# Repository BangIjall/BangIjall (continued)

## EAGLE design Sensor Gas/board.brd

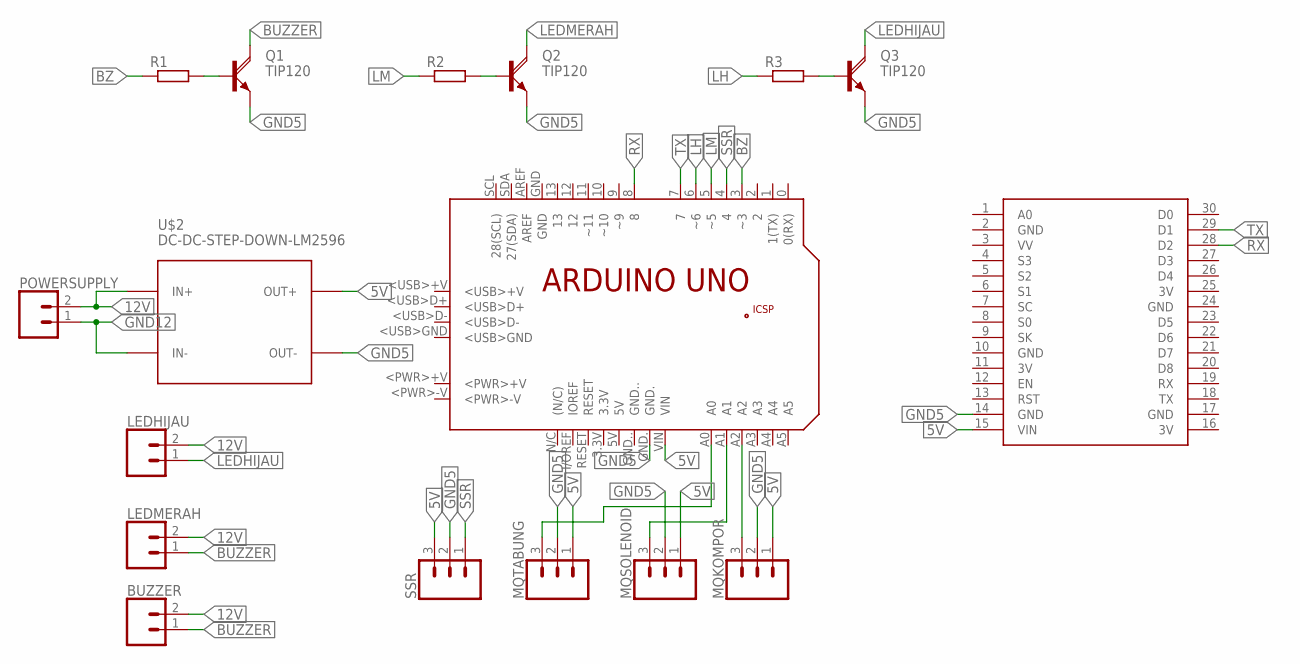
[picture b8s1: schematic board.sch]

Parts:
BUZZER: CONN_02; 1X02
LEDHIJAU: CONN_02; 1X02
LEDMERAH: CONN_02; 1X02
MQKOMPOR: CONN_03; 1X03
MQSOLENOID: CONN_03; 1X03
MQTABUNG: CONN_03; 1X03
PCB2: ARDUINO_UNO
POWERSUPPLY: CONN_02; 1X02
Q1, Q2, Q3: TIP120; TO220AH
R1, R2, R3: R-EU_0207/10; 0207/10
SSR: CONN_03; 1X03
U$1: NODEMCU
U$2: DC-DC-STEP-DOWN-LM2596

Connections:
3V: U$1.11 (3V), U$1.16 (3V), U$1.25 (3V)
5V: MQKOMPOR.1, MQSOLENOID.1, MQTABUNG.1, PCB2.VIN, SSR.3, U$1.15 (VIN), U$2.OUT+
12V: BUZZER.2, LEDHIJAU.2, LEDMERAH.2, POWERSUPPLY.2, U$2.IN+
BUZZER: BUZZER.1, LEDMERAH.1, Q1.C
BZ: PCB2.3 (~3), R1.1
GND: U$1.2 (GND), U$1.10 (GND), U$1.17 (GND), U$1.24 (GND)
GND5: MQKOMPOR.2, MQSOLENOID.2, MQTABUNG.2, PCB2.GND., Q1.E, Q2.E, Q3.E, SSR.2, U$1.14 (GND), U$2.OUT-
GND12: POWERSUPPLY.1, U$2.IN-
LEDHIJAU: LEDHIJAU.1, Q3.C
LEDMERAH: Q2.C
LH: PCB2.6 (~6), R3.1
LM: PCB2.5 (~5), R2.1
unnamed: Q1.B, R1.2
unnamed: MQSOLENOID.3, PCB2.A1
unnamed: MQTABUNG.3, PCB2.A0
unnamed: MQKOMPOR.3, PCB2.A2
unnamed: Q2.B, R2.2
unnamed: Q3.B, R3.2
RX: PCB2.8, U$1.28 (D2)
SSR: PCB2.4, SSR.1
TX: PCB2.7, U$1.29 (D1)

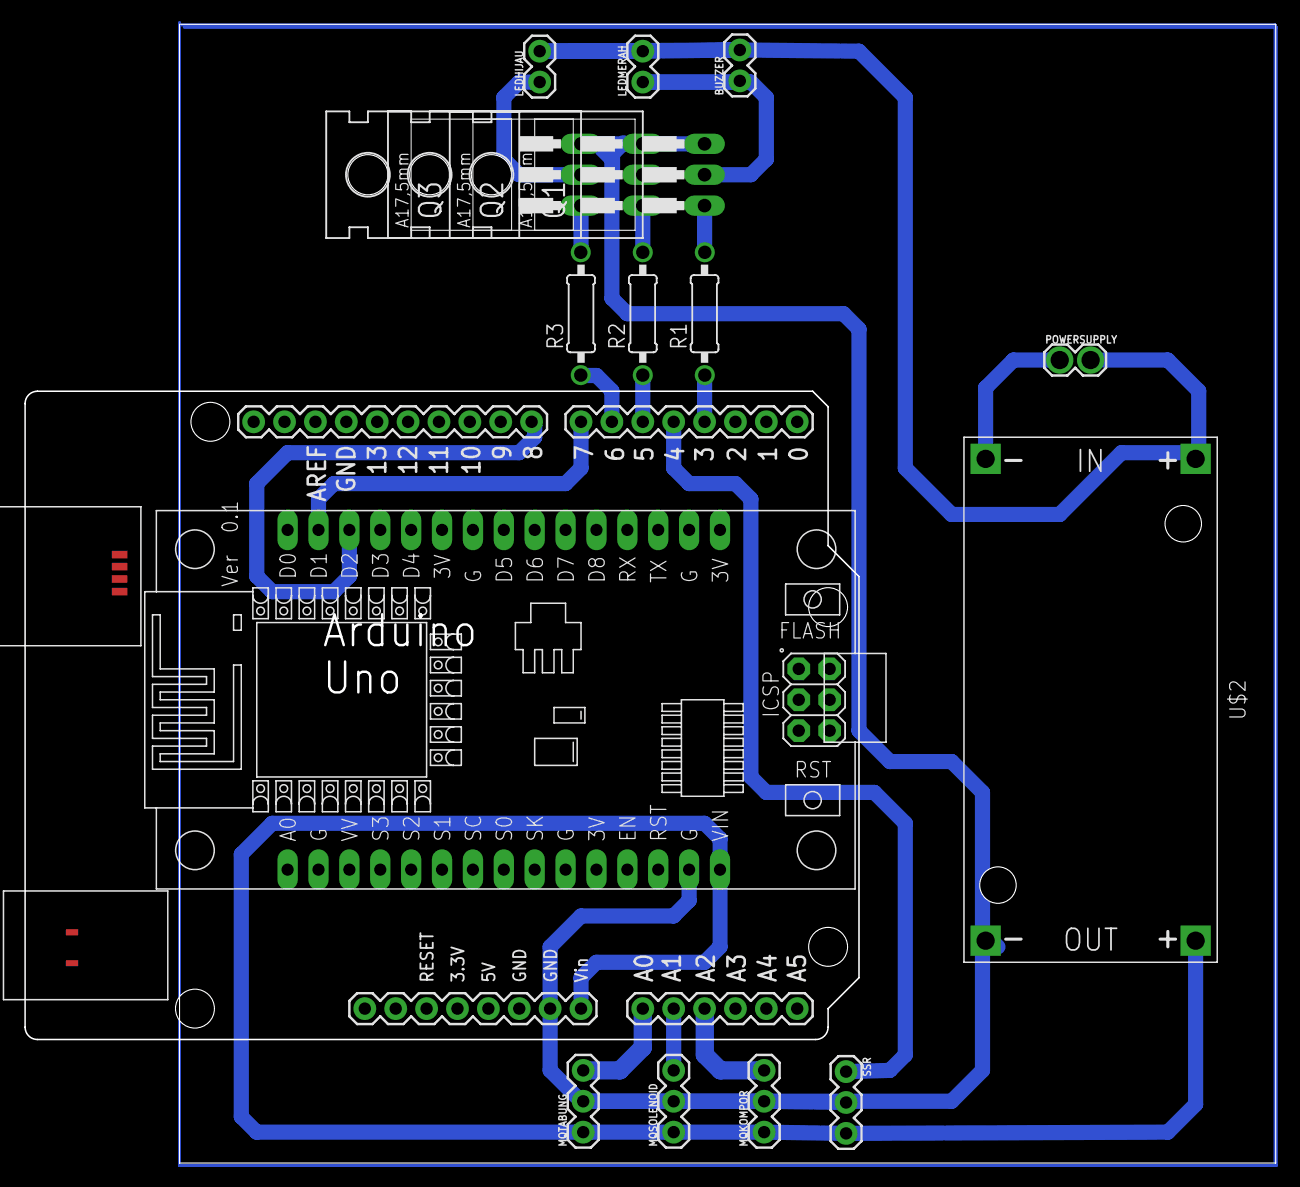
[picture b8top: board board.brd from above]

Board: 2 copper layers, 102.9 x 93.7 mm, 17 parts (0 on the bottom side), 20 nets.

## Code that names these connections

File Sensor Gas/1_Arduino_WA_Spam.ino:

#include <Arduino.h>
#include <SoftwareSerial.h>
#define rx_pin 8
#define tx_pin 7
SoftwareSerial data(rx_pin, tx_pin);
const float RL = 1;
const float clean_air_ratio = 10.0;
float adc, RS, Ro, RsRo, ppm, v;
float adc1, RS1, Ro1, RsRo1, ppm1, v1;
float adc2, RS2, Ro2, RsRo2, ppm2, v2;
const int SSR = 4;
const int buzzer = 3;
const int ledmerah = 5;
const int ledhijau = 6;
void kirimdata();
void setup()
{
  Serial.begin(9600);
  data.begin(115200);
  pinMode(buzzer, OUTPUT);
  pinMode(SSR, OUTPUT);
  pinMode(ledmerah, OUTPUT);
  pinMode(ledhijau, OUTPUT);
  pinMode(A0, INPUT);
  pinMode(A1, INPUT);
  pinMode(A2, INPUT);
  //sensor MQ di tabung
  int adc = analogRead(A0);
  v = adc * 5 / 1023.00;
  RS = ((5 * RL / v) - RL);
  Ro = RS / clean_air_ratio;
  delay(1000);

  //sensor MQ di SSR solenoid valve
  int adc1 = analogRead(A1);
  v1 = adc1 * 5 / 1023.00;
  RS1 = ((5 * RL / v1) - RL);
  Ro1 = RS1 / clean_air_ratio;
  delay(1000);

  //sensor MQ kompor
  int adc2 = analogRead(A2);
  v2 = adc2 * 5 / 1023.00;
  RS2 = ((5 * RL / v2) - RL);
  Ro2 = RS2 / clean_air_ratio;
  delay(1000);
}

void loop()
{
  kirimdata();
}

void kirimdata()
{
  //sensor MQ di tabung gas
  do
  {
  int adc = analogRead(A0);
  v = adc * 5 / 1023.00;
  RS = ((5 * RL / v) - RL);
  RsRo = RS / Ro;
  ppm = 1099.6 * pow((RsRo), -2.31);
  if (ppm >= 1000)
  {
    digitalWrite(buzzer, HIGH); // switch buzzer off
    digitalWrite(SSR, HIGH);
    digitalWrite(ledmerah, HIGH);
    digitalWrite(ledhijau, LOW);
    String datakirim = "a";
    Serial.println(datakirim);
    data.print(datakirim);
    data.write(13);
    delay(1000);
  }
  else
  {
    digitalWrite(buzzer, LOW); // switch buzzer on for 100ms
    digitalWrite(SSR, LOW);
    digitalWrite(ledmerah, LOW);
    digitalWrite(ledhijau, HIGH);
  }
  }
  while(ppm>=1000);

  //sensor MQ di SSR solenoid valve
  do
  {
  int adc1 = analogRead(A1);
  v1 = adc1 * 5 / 1023.00;
  RS1 = ((5 * RL / v1) - RL);
  RsRo1 = RS1 / Ro1;
  ppm1 = 1099.6 * pow((RsRo1), -2.31);

  if (ppm1 >= 1000)
  {
    digitalWrite(buzzer, HIGH); // switch buzzer off
    digitalWrite(SSR, HIGH);
    digitalWrite(ledmerah, HIGH);
    digitalWrite(ledhijau, LOW);
    String datakirim1 = "b";
    Serial.println(datakirim1);
    data.print(datakirim1);
    data.write(13);
    delay(1000);
  }
  else
  {
    digitalWrite(buzzer, LOW); // switch buzzer on for 100ms
    digitalWrite(SSR, LOW);
    digitalWrite(ledmerah, LOW);
    digitalWrite(ledhijau, HIGH);
  }
  }
   while(ppm1>=1000);

  //sensor MQ di kompor
  do
  {
  int adc2 = analogRead(A2);
  v2 = adc2 * 5 / 1023.00;
  RS2 = ((5 * RL / v2) - RL);
  RsRo2 = RS2 / Ro2;
  ppm2 = 1099.6 * pow((RsRo2), -2.31);

  if (ppm2 >= 1000)
  {
    digitalWrite(buzzer, HIGH); // switch buzzer off
    digitalWrite(SSR, HIGH);
    digitalWrite(ledmerah, HIGH);
    digitalWrite(ledhijau, LOW);
    String datakirim2 = "c";
    Serial.println(datakirim2);
    data.print(datakirim2);
    data.write(13);
    delay(1000);
  }
  else
  {
    digitalWrite(buzzer, LOW); // switch buzzer on for 100ms
    digitalWrite(SSR, LOW);
    digitalWrite(ledmerah, LOW);
    digitalWrite(ledhijau, HIGH);
  }
  }
   while(ppm2>=1000);

  //sediakan variabel data yang akan dikirm
  Serial.println("ppm0 : " + (String)ppm + ", ppm1 : " + (String)ppm1 + " ppm2 : " + (String)ppm2);
  delay(1000);
}

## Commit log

2021-06-30 backup
2021-06-30 baru
2021-07-01 mask detector
2021-07-14 baru xixi
2021-07-24 mbak dhita
2021-07-24 mbak dhita fixxx
2021-07-25 alhamdulillah mbak dhita kelar
2021-12-15 xixixi
2021-12-20 download yg ini ya ayuk & nisa
2021-12-20 programnya gausah didownload
